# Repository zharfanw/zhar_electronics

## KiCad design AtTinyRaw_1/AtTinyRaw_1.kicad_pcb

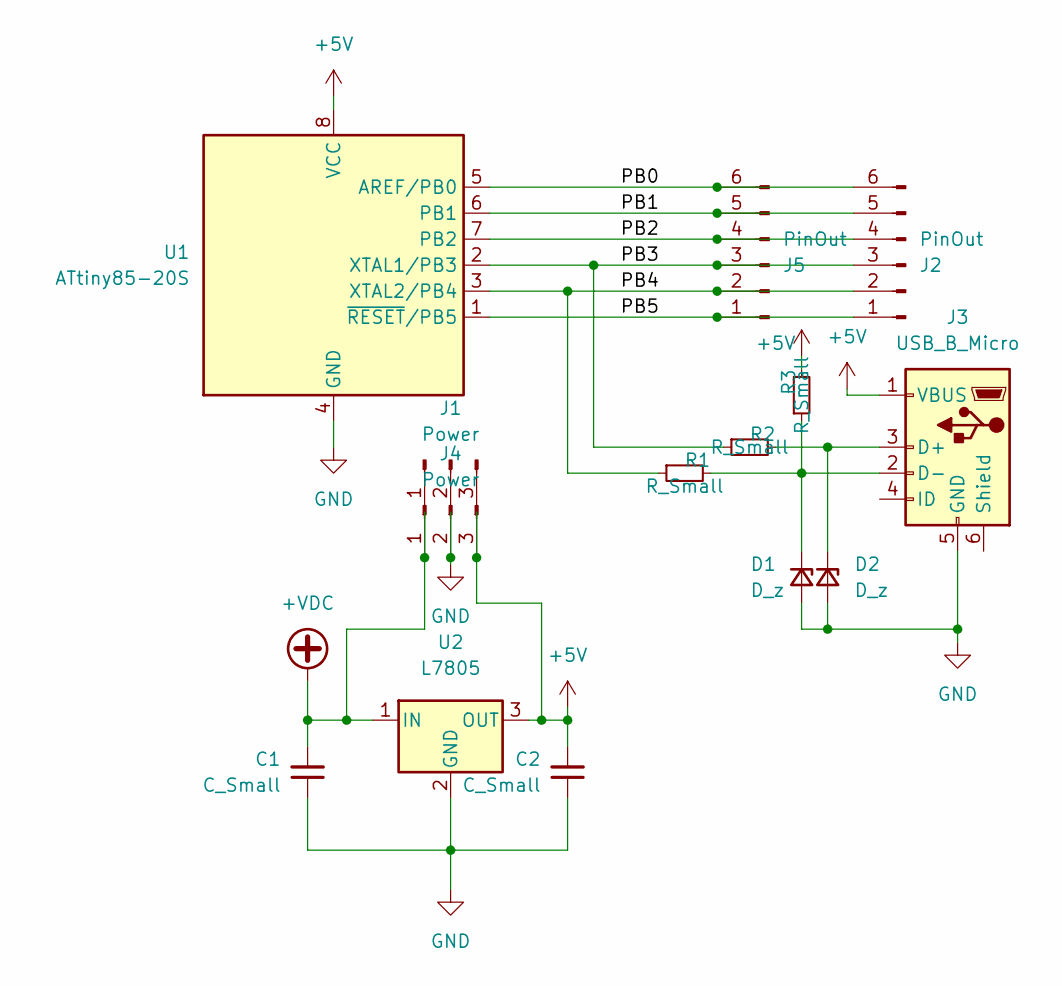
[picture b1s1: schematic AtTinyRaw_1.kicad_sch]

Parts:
C1, C2: C_Small; C_0805_2012Metric_Pad1.18x1.45mm_HandSolder
D1, D2: D_z; D_1206_3216Metric_Pad1.42x1.75mm_HandSolder
J1, J4: Power; PinSocket_1x03_P2.54mm_Vertical
J2, J5: PinOut; PinSocket_1x06_P2.54mm_Vertical
J3: USB_B_Micro; USB_Micro-AB_Molex_47590-0001
R1, R2, R3: R_Small; R_0805_2012Metric_Pad1.20x1.40mm_HandSolder
U1: ATtiny85-20S; SOIC-8W_5.3x5.3mm_P1.27mm
U2: L7805; TO-252-2

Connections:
+5V: C2.2, J1.3, J3.1 (VBUS), J4.3, R3.2, U1.8 (VCC), U2.3 (OUT)
+VDC: C1.2, J1.1, J4.1, U2.1 (IN)
/PB0: J2.6, J5.6, U1.5 (AREF/PB0)
/PB1: J2.5, J5.5, U1.6 (PB1)
/PB2: J2.4, J5.4, U1.7 (PB2)
/PB3: J2.3, J5.3, R2.1, U1.2 (XTAL1/PB3)
/PB4: J2.2, J5.2, R1.1, U1.3 (XTAL2/PB4)
/PB5: J2.1, J5.1, U1.1 (~RESET/PB5)
GND: C1.1, C2.1, D1.2 (A), D2.2 (A), J1.2, J3.5 (GND), J4.2, U1.4 (GND), U2.2 (GND)
unnamed: D1.1 (K), J3.2 (D-), R1.2, R3.1
unnamed: D2.1 (K), J3.3 (D+), R2.2

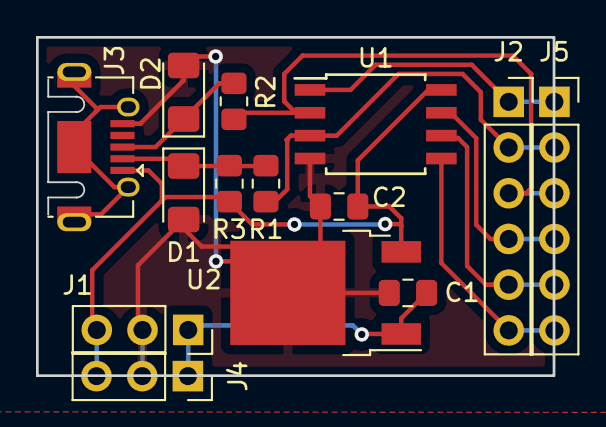
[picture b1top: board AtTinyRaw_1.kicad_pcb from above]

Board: 2 copper layers, 28.7 x 18.8 mm, 14 parts (0 on the bottom side), 11 nets.

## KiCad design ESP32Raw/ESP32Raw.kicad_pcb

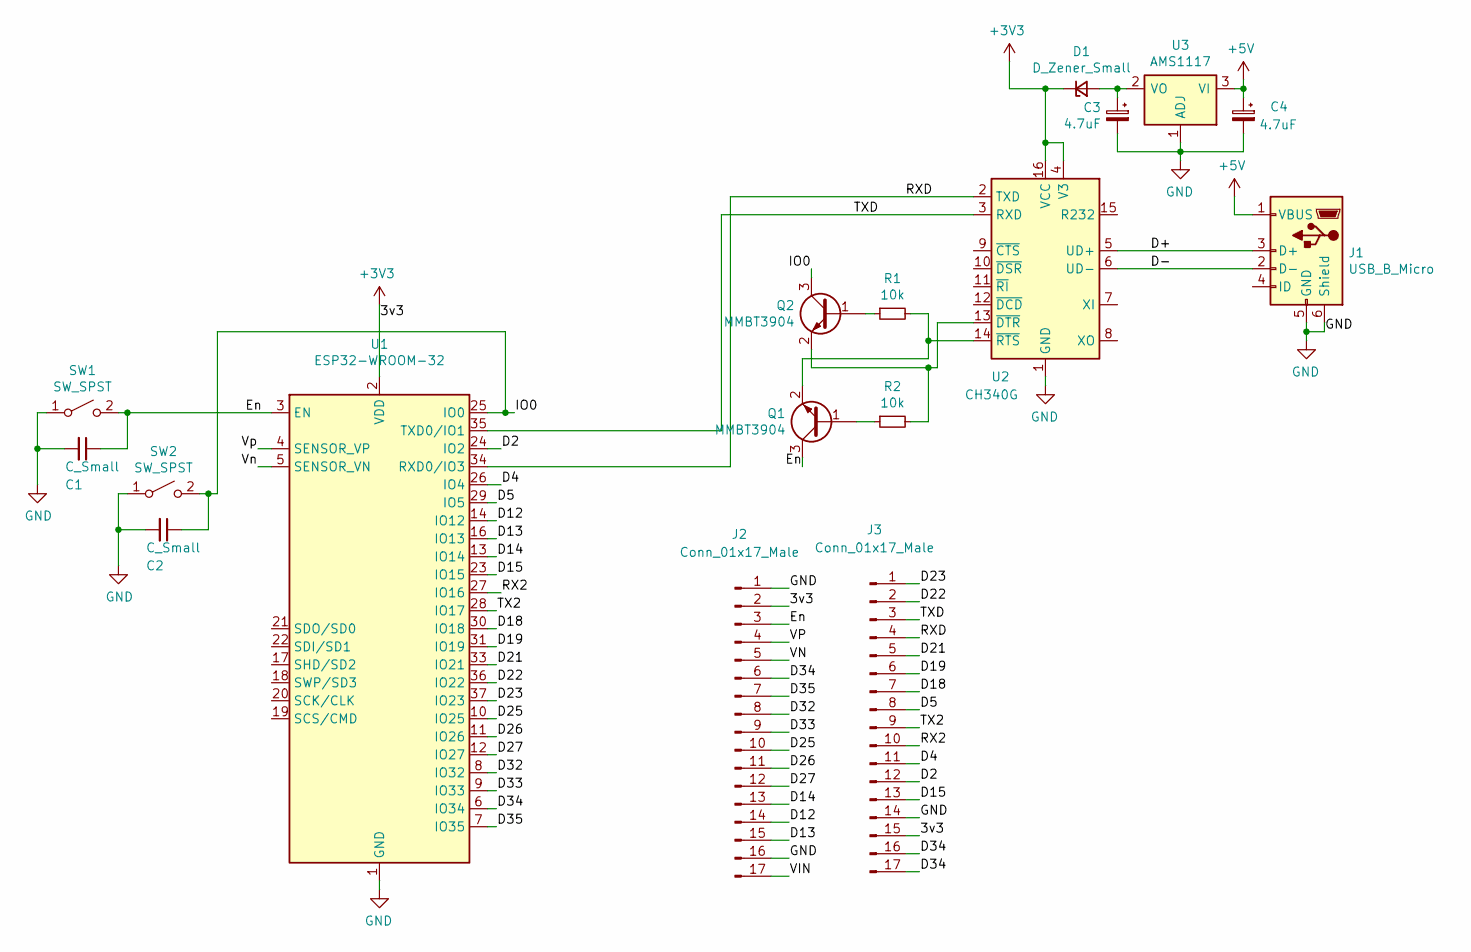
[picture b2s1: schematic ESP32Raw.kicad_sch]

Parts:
C1, C2: C_Small; C_0805_2012Metric_Pad1.18x1.45mm_HandSolder
C3, C4: 4.7uF; C_0805_2012Metric_Pad1.18x1.45mm_HandSolder
D1: D_Zener_Small; D_SOD-323
J1: USB_B_Micro; USB_Micro-B_Molex-105017-0001
J2, J3: Conn_01x17_Male; PinHeader_1x17_P2.54mm_Vertical
Q1, Q2: MMBT3904; SOT-23
R1, R2: 10k; R_0805_2012Metric_Pad1.20x1.40mm_HandSolder
SW1, SW2: SW_SPST; SW_SPST_EVQPE1
U1: ESP32-WROOM-32
U2: CH340G; SOIC-16_3.9x9.9mm_P1.27mm
U3: AMS1117; SOT-223-3_TabPin2

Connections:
+3V3: D1.1 (K), J2.2, J3.15, U1.2 (VDD), U2.4 (V3), U2.16 (VCC)
+5V: C4.1, J1.1 (VBUS), U3.3 (VI)
/D2: J3.12, U1.24 (IO2)
/D4: J3.11, U1.26 (IO4)
/D5: J3.8, U1.29 (IO5)
/D12: J2.14, U1.14 (IO12)
/D13: J2.15, U1.16 (IO13)
/D14: J2.13, U1.13 (IO14)
/D15: J3.13, U1.23 (IO15)
/D18: J3.7, U1.30 (IO18)
/D19: J3.6, U1.31 (IO19)
/D21: J3.5, U1.33 (IO21)
/D22: J3.2, U1.36 (IO22)
/D23: J3.1, U1.37 (IO23)
/D25: J2.10, U1.10 (IO25)
/D26: J2.11, U1.11 (IO26)
/D27: J2.12, U1.12 (IO27)
/D32: J2.8, U1.8 (IO32)
/D33: J2.9, U1.9 (IO33)
/D34: J2.6, J3.16, J3.17, U1.6 (IO34)
/D35: J2.7, U1.7 (IO35)
/D+: J1.3 (D+), U2.5 (UD+)
/D-: J1.2 (D-), U2.6 (UD-)
/En: C1.1, J2.3, Q1.3 (C), SW1.2 (B), U1.3 (EN)
/IO0: C2.1, Q2.3 (C), SW2.2 (B), U1.25 (IO0)
/RX2: J3.10, U1.27 (IO16)
/RXD: J3.4, U1.34 (RXD0/IO3), U2.2 (TXD)
/TX2: J3.9, U1.28 (IO17)
/TXD: J3.3, U1.35 (TXD0/IO1), U2.3 (RXD)
/VIN: J2.17
/VN: J2.5
/VP: J2.4
/Vn: U1.5 (SENSOR_VN)
/Vp: U1.4 (SENSOR_VP)
GND: C1.2, C2.2, C3.2, C4.2, J1.5 (GND), J1.6 (Shield), J2.1, J2.16, J3.14, SW1.1 (A), SW2.1 (A), U1.1 (GND), U1.15 (GND), U1.38 (GND), U1.39 (GND), U2.1 (GND), U3.1 (ADJ)
unnamed: C3.1, D1.2 (A), U3.2 (VO)
unnamed: Q1.1 (B), R2.1
unnamed: Q1.2 (E), R1.2, U2.14 (~RTS)
unnamed: Q2.1 (B), R1.1
unnamed: Q2.2 (E), R2.2, U2.13 (~DTR)

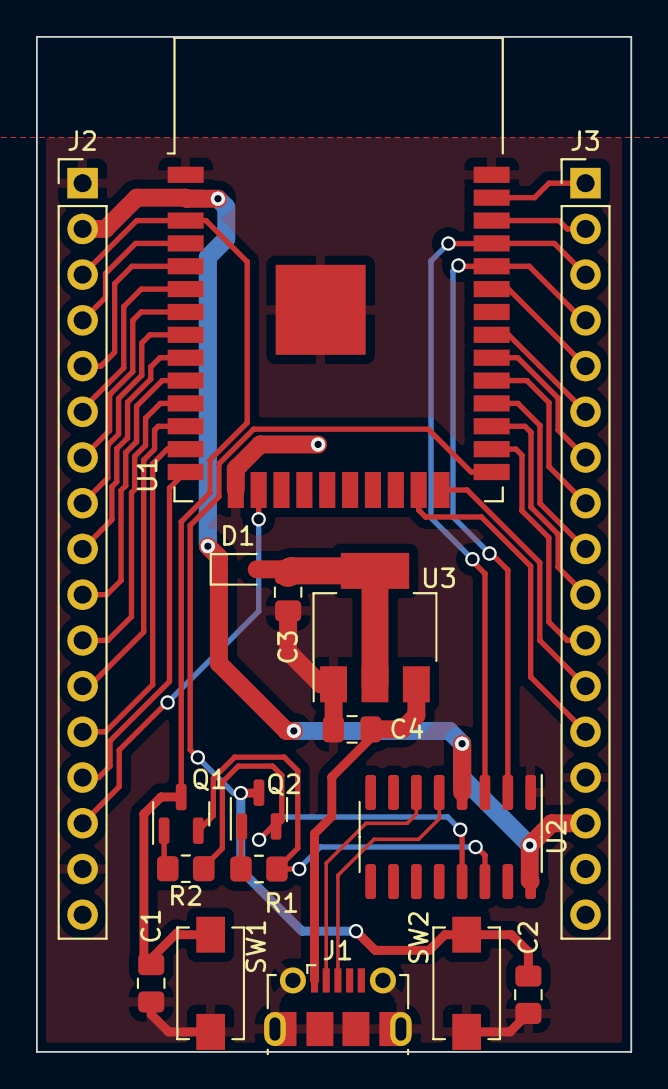
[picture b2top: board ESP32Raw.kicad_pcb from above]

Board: 2 copper layers, 33.0 x 56.4 mm, 17 parts (0 on the bottom side), 35 nets.

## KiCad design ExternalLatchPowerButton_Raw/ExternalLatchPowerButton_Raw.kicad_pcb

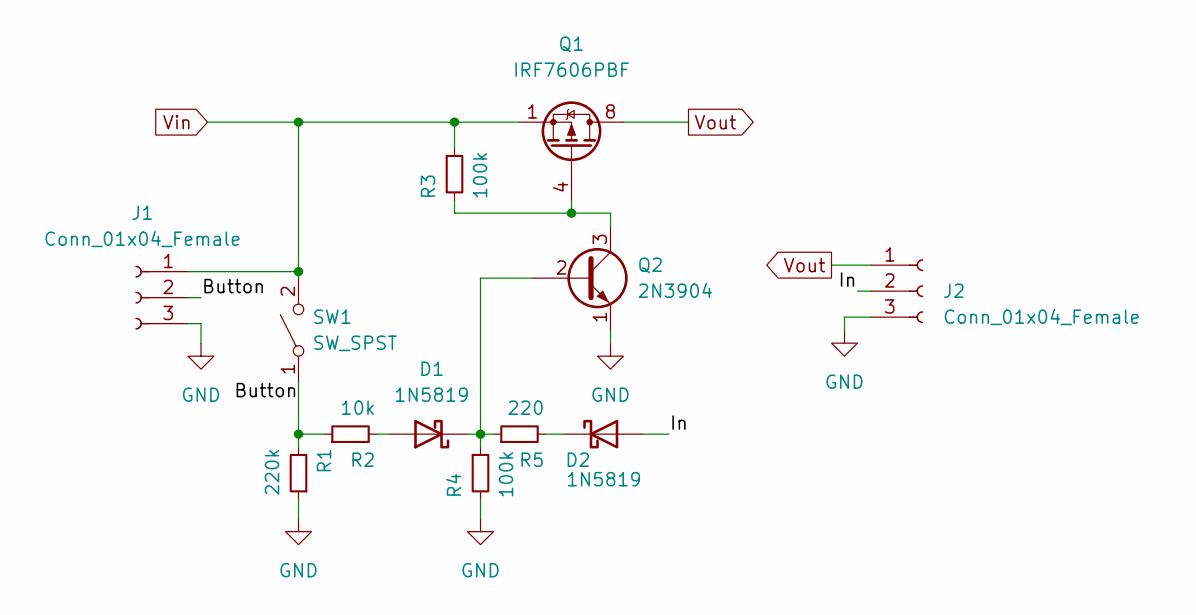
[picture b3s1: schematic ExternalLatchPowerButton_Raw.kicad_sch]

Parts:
D1, D2: 1N5819; D_SOD-123
J1, J2: Conn_01x04_Female; PinSocket_1x03_P2.54mm_Vertical
Q1: IRF7606PBF; MSOP-8_3x3mm_P0.65mm
Q2: 2N3904; SOT-23
R1: 220k; R_0805_2012Metric
R2: 10k; R_0805_2012Metric
R3, R4: 100k; R_0805_2012Metric
R5: 220; R_0805_2012Metric
SW1: SW_SPST; SW_SPST_SKQG_WithoutStem

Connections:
/Button: J1.2, R1.2, R2.1, SW1.1 (A)
/In: D2.2 (A), J2.2
GND: J1.3, J2.3, Q2.1 (E), R1.1, R4.2
unnamed: D1.1 (K), Q2.2 (B), R4.1, R5.1
unnamed: D1.2 (A), R2.2
unnamed: D2.1 (K), R5.2
unnamed: Q1.4 (G), Q2.3 (C), R3.2
Vin: J1.1, Q1.1 (S), Q1.2 (S), Q1.3 (S), R3.1, SW1.2 (B)
Vout: J2.1, Q1.5 (D), Q1.6 (D), Q1.7 (D), Q1.8 (D)

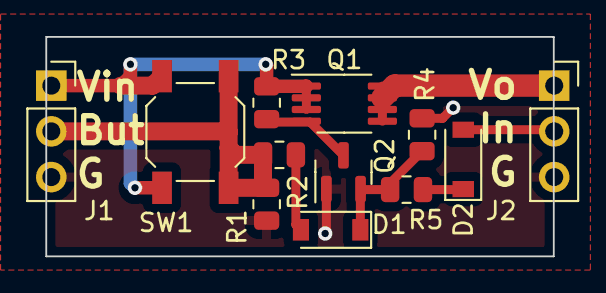
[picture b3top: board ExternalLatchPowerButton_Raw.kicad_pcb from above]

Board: 2 copper layers, 28.2 x 12.2 mm, 12 parts (0 on the bottom side), 9 nets.

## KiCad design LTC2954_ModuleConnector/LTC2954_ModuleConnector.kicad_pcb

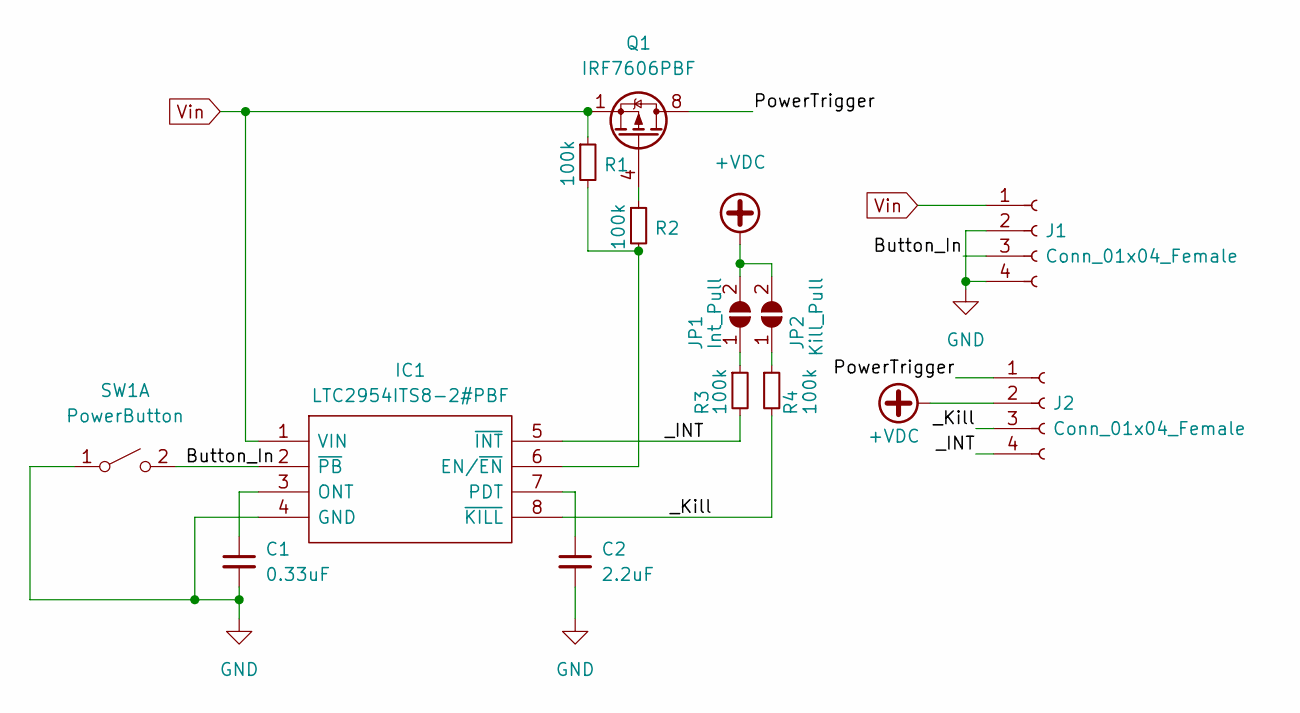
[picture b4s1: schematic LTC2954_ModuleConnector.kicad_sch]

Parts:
C1: 0.33uF; C_0805_2012Metric
C2: 2.2uF; C_0805_2012Metric
IC1: LTC2954ITS8-2#PBF; SOT65P280X100-8N; Manufacturer_Part_Number LTC2954ITS8-2#PBF; Mouser Part Number 584-LTC2954ITS8-2PBF
J1, J2: Conn_01x04_Female; PinSocket_1x04_P2.54mm_Vertical
JP1: Int_Pull; SolderJumper-2_P1.3mm_Open_TrianglePad1.0x1.5mm
JP2: Kill_Pull; SolderJumper-2_P1.3mm_Open_TrianglePad1.0x1.5mm
Q1: IRF7606PBF; MSOP-8_3x3mm_P0.65mm
R1, R2, R3, R4: 100k; R_0805_2012Metric
SW1: PowerButton; SW_Push_1P1T_NO_CK_KMR2

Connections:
+VDC: J2.2, JP1.2 (B), JP2.2 (B)
/Button_In: IC1.2 (~PB), J1.3, SW1.2 (B)
/PowerTrigger: J2.1, Q1.5 (D), Q1.6 (D), Q1.7 (D), Q1.8 (D)
/_INT: IC1.5 (~INT), J2.4, R3.2
/_Kill: IC1.8 (~KILL), J2.3, R4.2
GND: C1.2, C2.2, IC1.4 (GND), J1.2, J1.4, SW1.1 (A)
unnamed: C1.1, IC1.3 (ONT)
unnamed: C2.1, IC1.7 (PDT)
unnamed: IC1.6 (EN/~EN), R1.2, R2.2
unnamed: JP1.1 (A), R3.1
unnamed: JP2.1 (A), R4.1
unnamed: Q1.4 (G), R2.1
Vin: IC1.1 (VIN), J1.1, Q1.1 (S), Q1.2 (S), Q1.3 (S), R1.1

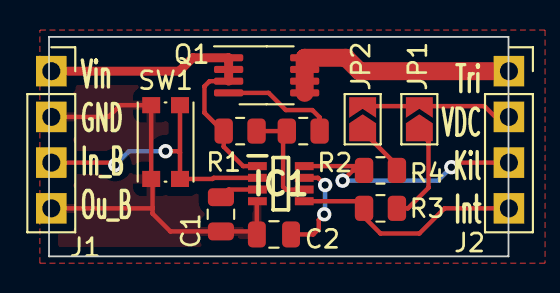
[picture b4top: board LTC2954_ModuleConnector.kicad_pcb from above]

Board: 2 copper layers, 25.5 x 12.2 mm, 13 parts (0 on the bottom side), 13 nets.

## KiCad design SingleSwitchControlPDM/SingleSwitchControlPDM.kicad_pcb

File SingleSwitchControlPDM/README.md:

# Single Switch Control PDM
Rangkaian Elektronik untuk mengontrol Arus listrik 
## Biaya

## Simulation

##

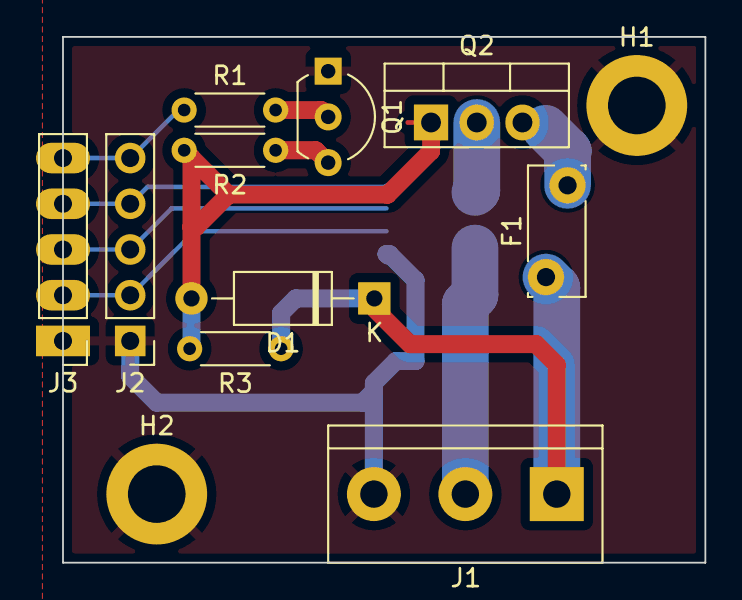
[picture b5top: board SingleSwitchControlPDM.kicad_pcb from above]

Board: 2 copper layers, 35.7 x 29.2 mm, 13 parts (1 on the bottom side), 12 nets.

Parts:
D1: D_Small; D_A-405_P10.16mm_Horizontal
F1: Fuse; Fuse_Bourns_MF-RG300
H1, H2: MountingHole_Pad; MountingHole_3.2mm_M3_DIN965_Pad
J1: Screw_Terminal_01x02; TerminalBlock_bornier-3_P5.08mm
J2, J3: Conn_01x05_Male; PinHeader_1x05_P2.54mm_Vertical
Q1: 2N2219; TO-92L_Inline_Wide
Q2: IRF9540N; TO-220-3_Vertical
R1, R2, R3: R_Small; R_Axial_DIN0204_L3.6mm_D1.6mm_P5.08mm_Horizontal
U1: ACS712xLCTR-30A; SOIC-8_3.9x4.9mm_P1.27mm

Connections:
+5V: J2.4, J3.4, U1.8 (VCC)
+VDC: D1.1 (K), F1.1, J1.1, R3.1
/2_30Amp: Q2.2 (D), U1.1 (IP+), U1.2 (IP+)
/3_30Amp: J1.2, U1.3 (IP-), U1.4 (IP-)
/30Amp: F1.2, Q2.3 (S)
/Filter: J2.2, J3.2, U1.6 (FILTER)
/Input: J2.5, J3.5, R1.1
/Vout: J2.3, J3.3, U1.7 (VIOUT)
GND: H1.1, H2.1, J1.3, J2.1, J3.1, Q1.1 (E), U1.5 (GND)
unnamed: D1.2 (A), Q2.1 (G), R2.2, R3.2
unnamed: Q1.2 (B), R1.2
unnamed: Q1.3 (C), R2.1

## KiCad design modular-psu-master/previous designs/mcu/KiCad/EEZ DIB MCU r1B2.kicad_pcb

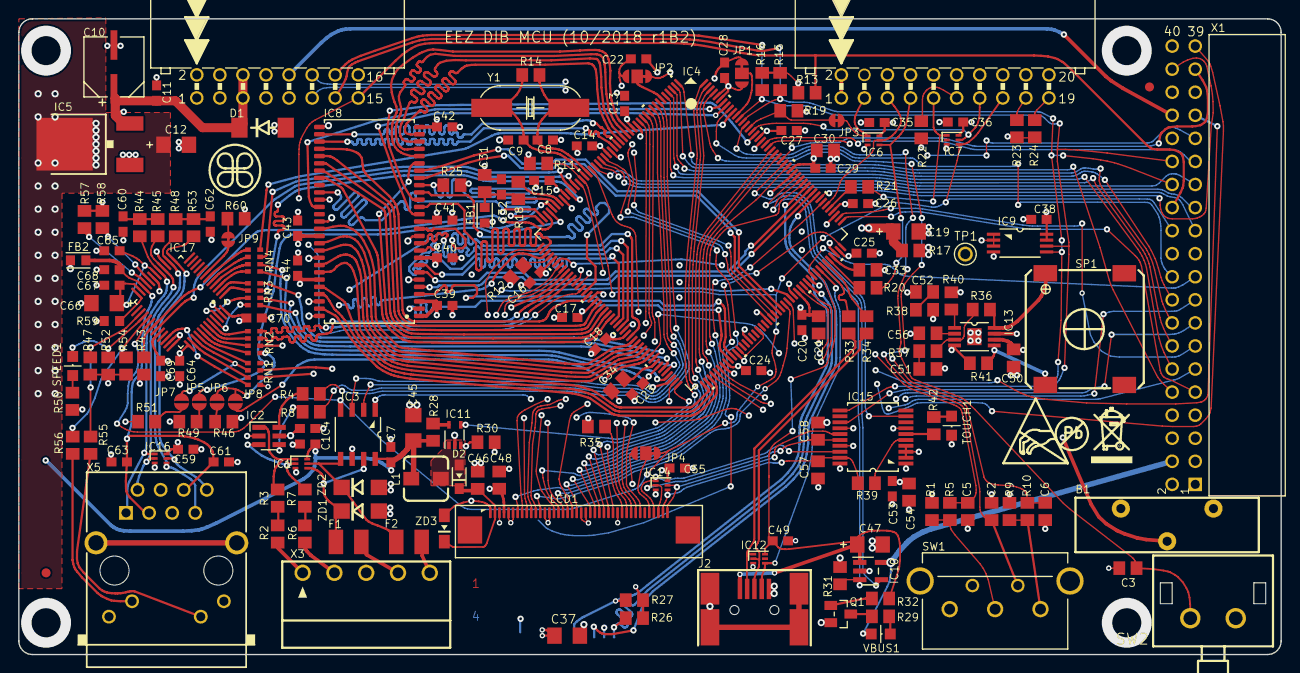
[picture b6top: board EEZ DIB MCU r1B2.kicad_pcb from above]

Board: 4 copper layers, 139.0 x 70.0 mm, 194 parts (0 on the bottom side), 233 nets.

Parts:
B1: DS1092-16-B6P
C1, C4, C7, C11, C13, C14, C15, C16, C17, C18, C20, C23, C24, C25, C26, C27, C28, C29, C32, C35, C36, C38, C39, C40, C41, C42, C43, C44, C49, C53, C55, C59, C60, C61, C62, C63, C64, C65, C67, C68, C69, C70: 100n; C0603
C2, C3, C5, C6, C57, C58: 10n; C0805
C8, C9: 18p; C0603
C10: EEEFK1V470P; CAPAE660X610N
C12, C19, C47: 4u7; EC1206
C21, C30, C31, C46, C50, C54: 1u; C0805
C22: N.C.; C0603
C33, C34, C48: 2u2; C0805
C37, C45: 4u7; C1206
C51, C52, C56: 470n; C0805
C66: 10u; EC1206
D1: SMBJ5.0A-TR; DO214AA
D2: RB751V40T1G or NSR0240; SOD323-R
EEZ_SIGNATURE: SIGNATURESMALL; SIGNATURE_5MM
F1, F2: 50mA; F1210
FB1, FB2: LCBA-600; BEAD0603
FM1, FM2: FIDUCIAL
IC1, IC6, IC7, IC12, IC14, IC16: TPD4E001DRLR; DRL6
IC2: SN74LVC2G34DBVR; DBV6
IC3: BTS3408G; SOIC127P600X173-8N
IC4: STM32F769IGT6; LQFP-176_24X24MM
IC5: LD1117ADT33TR; DPACK
IC8: IS42S16400J; TSOPII-54
IC9: BR24G64FVT-3AGE2; PW8_TSSOP8
IC10: TPS2051BDBVR; DBV5
IC11: TPS61169DCKR; DCK5
IC13: TPA6205A1DGN; SOP65P490X110-9N
IC15: AR1021-I/SS; SOP65P780X200-20N
IC17: DP83848CVV_NOPB; PT48
J1: 503398-1892; 5033981892
J2: 67803-8020; 678038020
JP1, JP2, JP4: JP3-CUT
JP3, JP9: JP2-NOCUT
JP5, JP6, JP7, JP8: JP2-CUT
L1: DLG-0403-4R7; DE0403
LCD1: PCA-6-LA-40-HL-3; FPC_40
Q1: MMBT5551; SOT23-BEC
R1, R2, R3, R6, R7, R9, R13, R15, R16, R42: 4K7; R0805
R4, R8: 1K; R0805
R5, R10, R11, R12, R22, R23, R24, R25, R35, R37, R38: 10K; R0805
R14: 1M; R0805
R17: 0R; R0805
R18: 47R; R0805
R19, R26, R27, R29, R31, R32, R40: 47K; R0805
R20, R21, R33, R34: 22R; R0805
R28, R30: 10R; R0805
R36, R39, R41: 20K; R0805
R43: 1K5; R0805
R44, R45, R48, R53: 49R9; R0805
R46, R47, R49, R51, R52, R54, R57, R58, R60: 2K2; R0805
R50, R55, R56: 220R; R0805
R59: 4K87; R0603
RN1, RN2, RN3, RN4: DR1206-33R-4/8; CAY16
SP1: LD-BZEL-M1313
SPEED1: LTST-C170YKT; LED_0805
SW1: PEC16-2215F-S0024; PEC16-2215F
SW2: TL1100CF160Q; TL1100C
TOUCH1: HSMY-C170; LED_0805
TP1: PCB_TEST_TABSHIELD; PCB_SHIELD_TAB
U$1: RECYCLE_BIN1_8
U$5: PB_SMALL
U$6: ESD_SYMBOL
VBUS1: HSMG-C170; LED_0805
X1: ZL263-40DG
X2: ZL231-16KG; ML16L
X3: 1844249; MC1,5_5-G-3,5
X4: ZL231-20KG; ML20L
X5: LMJTAB881243M-L; RJ45-TRAFO-LED
Y1: 10MHz; HC-49_4H
ZD1, ZD2: SMAJ18A; DO214AC
ZD3: BZX384-B30.115; SOD323-W

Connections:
+3V3: C4.1, C12.+, C35.1, C36.1, C37.1, C38.2, C39.1, C40.1, C41.1, C42.1, C43.1, C44.1, C48.1, C50.2, C53.2, C54.2, C55.2, C59.1, C69.1, C70.1, FB2.P$1, IC2.5, IC5.4, IC6.6, IC7.6, IC8.1, IC8.3, IC8.9, IC8.14, IC8.27, IC8.43, IC8.49, IC9.1, IC9.2, IC9.3, IC9.7, IC9.8, IC13.6, IC14.6, IC15.1, IC16.6, IC17.32, IC17.48, J1.4, LCD1.4, R1.1, R9.1, R13.1, R15.1, R16.1, R17.1, R19.1, R25.1, R26.1, R27.1, R31.2, R35.2, R40.2, R43.2, R47.1, R50.1, R51.1, R52.1, R54.1, R57.1, R58.1, R60.1, X1.32, X2.16, X4.1, X4.2, X5.9, X5.12
+3V3(A): C61.2, C63.2, C68.1, FB2.P$2, IC17.22, X5.3, X5.6
+5V: C1.1, C7.2, C10.1, C11.1, C45.1, D1.C, IC1.6, IC3.8, IC5.3, IC10.5, L1.1, R28.1, VBUS1.A, X1.3, X1.4, X2.5, X2.6
+12V: X1.5, X1.6, X2.3, X2.4
/Ethernet PHY/ETH_COL: IC4.47, RN2.2
/Ethernet PHY/ETH_CRS: IC4.40, JP5.1, RN1.4
/Ethernet PHY/ETH_MDC: IC4.33, IC17.31
/Ethernet PHY/ETH_MDIO: IC4.42, IC17.30, R43.1
/Ethernet PHY/ETH_RX+: IC16.4, IC17.14, R48.2, X5.7
/Ethernet PHY/ETH_RX-: IC16.5, IC17.13, R53.1, X5.8
/Ethernet PHY/ETH_RXD0: IC4.54, RN2.3
/Ethernet PHY/ETH_RXD1: IC4.55, RN2.4
/Ethernet PHY/ETH_RXD2: IC4.83, RN3.1
/Ethernet PHY/ETH_RXD3: IC4.84, RN3.2
/Ethernet PHY/ETH_RX_CLK: IC4.41, RN1.2
/Ethernet PHY/ETH_RX_DV: IC4.53, RN1.3
/Ethernet PHY/ETH_TX+: IC16.1, IC17.17, R44.2, X5.1
/Ethernet PHY/ETH_TX-: IC16.2, IC17.16, R45.1, X5.2
/Ethernet PHY/ETH_TXD0: IC4.85, RN4.1
/Ethernet PHY/ETH_TXD1: IC4.86, RN4.2
/Ethernet PHY/ETH_TXD2: IC4.34, RN4.3
/Ethernet PHY/ETH_TXD3: IC4.167, RN4.4
/Ethernet PHY/ETH_TX_CLK: IC4.35, RN3.3
/Ethernet PHY/ETH_TX_EN: IC4.80, RN3.4
/Ethernet PHY/LED_ACT: IC17.26, R47.2, R55.2
/Ethernet PHY/LED_LINK: IC17.28, R54.2, R56.2
/Ethernet PHY/LED_SPEED: IC17.27, R52.2, SPEED1.C
/Ethernet PHY/MCLK_25: IC4.122, RN1.1
/I/O connectors, encoders, user SW/+VAUX: X1.34, X2.10
/I/O connectors, encoders, user SW/ENC_A: C5.2, IC4.119, R5.1
/I/O connectors, encoders, user SW/ENC_B: C6.1, IC4.120, R10.1
/I/O connectors, encoders, user SW/ENC_SW: C2.2, IC4.173, SW1.E
/I/O connectors, encoders, user SW/USER_SW: C3.2, IC4.163, SW2.1
/SDRAM, JTAG, SD card, EEPROM/DBGACK: R24.1, X4.19
/SDRAM, JTAG, SD card, EEPROM/DBGRQ: R23.1, X4.17
/SDRAM, JTAG, SD card, EEPROM/FMC_A0: IC4.16, IC8.23
/SDRAM, JTAG, SD card, EEPROM/FMC_A1: IC4.17, IC8.24
/SDRAM, JTAG, SD card, EEPROM/FMC_A2: IC4.18, IC8.25
/SDRAM, JTAG, SD card, EEPROM/FMC_A3: IC4.19, IC8.26
/SDRAM, JTAG, SD card, EEPROM/FMC_A4: IC4.20, IC8.29
/SDRAM, JTAG, SD card, EEPROM/FMC_A5: IC4.21, IC8.30
/SDRAM, JTAG, SD card, EEPROM/FMC_A6: IC4.60, IC8.31
/SDRAM, JTAG, SD card, EEPROM/FMC_A7: IC4.63, IC8.32
/SDRAM, JTAG, SD card, EEPROM/FMC_A8: IC4.64, IC8.33
/SDRAM, JTAG, SD card, EEPROM/FMC_A9: IC4.65, IC8.34
/SDRAM, JTAG, SD card, EEPROM/FMC_A10: IC4.66, IC8.22
/SDRAM, JTAG, SD card, EEPROM/FMC_A11: IC4.67, IC8.35
/SDRAM, JTAG, SD card, EEPROM/FMC_BA0: IC4.112, IC8.20
/SDRAM, JTAG, SD card, EEPROM/FMC_BA1: IC4.113, IC8.21
/SDRAM, JTAG, SD card, EEPROM/FMC_D0: IC4.97, IC8.2
/SDRAM, JTAG, SD card, EEPROM/FMC_D1: IC4.98, IC8.4
/SDRAM, JTAG, SD card, EEPROM/FMC_D2: IC4.142, IC8.5
/SDRAM, JTAG, SD card, EEPROM/FMC_D3: IC4.143, IC8.7
/SDRAM, JTAG, SD card, EEPROM/FMC_D4: IC4.68, IC8.8
/SDRAM, JTAG, SD card, EEPROM/FMC_D5: IC4.69, IC8.10
/SDRAM, JTAG, SD card, EEPROM/FMC_D6: IC4.70, IC8.11
/SDRAM, JTAG, SD card, EEPROM/FMC_D7: IC4.73, IC8.13
/SDRAM, JTAG, SD card, EEPROM/FMC_D8: IC4.74, IC8.42
/SDRAM, JTAG, SD card, EEPROM/FMC_D9: IC4.75, IC8.44
/SDRAM, JTAG, SD card, EEPROM/FMC_D10: IC4.76, IC8.45
/SDRAM, JTAG, SD card, EEPROM/FMC_D11: IC4.77, IC8.47
/SDRAM, JTAG, SD card, EEPROM/FMC_D12: IC4.78, IC8.48
/SDRAM, JTAG, SD card, EEPROM/FMC_D13: IC4.89, IC8.50
/SDRAM, JTAG, SD card, EEPROM/FMC_D14: IC4.90, IC8.51
/SDRAM, JTAG, SD card, EEPROM/FMC_D15: IC4.91, IC8.53
/SDRAM, JTAG, SD card, EEPROM/FMC_NBL0: IC4.169, IC8.15
/SDRAM, JTAG, SD card, EEPROM/FMC_NBL1: IC4.170, IC8.39
/SDRAM, JTAG, SD card, EEPROM/FMC_SDCKE0: IC4.43, IC8.37
/SDRAM, JTAG, SD card, EEPROM/FMC_SDCLK: IC4.116, IC8.38
/SDRAM, JTAG, SD card, EEPROM/FMC_SDNCAS: IC4.160, IC8.17
/SDRAM, JTAG, SD card, EEPROM/FMC_SDNE0: IC4.44, IC8.19, R25.2
/SDRAM, JTAG, SD card, EEPROM/FMC_SDNRAS: IC4.59, IC8.18
/SDRAM, JTAG, SD card, EEPROM/FMC_SDNWE: IC4.46, IC8.16
/SDRAM, JTAG, SD card, EEPROM/RTCK: R22.1, X4.11
/SDRAM, JTAG, SD card, EEPROM/SDMMC1_CK: IC4.141, J1.5
/SDRAM, JTAG, SD card, EEPROM/SDMMC1_CMD: IC4.144, J1.3, R27.2
/SDRAM, JTAG, SD card, EEPROM/SDMMC1_D0: IC4.121, J1.7, R26.2
/SDRAM, JTAG, SD card, EEPROM/SD_DETECT: IC4.24, J1.SW1
/SDRAM, JTAG, SD card, EEPROM/SYS_JTCK-SWCLK: IC4.137, R21.1
/SDRAM, JTAG, SD card, EEPROM/SYS_JTDI: IC4.138, IC6.5, X4.5
/SDRAM, JTAG, SD card, EEPROM/SYS_JTDO-SWO: IC4.161, IC7.5, X4.13
/SDRAM, JTAG, SD card, EEPROM/SYS_JTMS-SWDIO: IC4.128, R20.1
/SDRAM, JTAG, SD card, EEPROM/SYS_JTRST: IC4.162, JP3.1, R19.2
/SDRAM, JTAG, SD card, EEPROM/TCK: IC7.1, R21.2, X4.9
/SDRAM, JTAG, SD card, EEPROM/TMS: IC6.4, R20.2, X4.7
/STM32F7 MCU/BOOT0: IC4.166, JP1.COM
/STM32F7 MCU/BYPASS_REG: IC4.48, R12.2
/STM32F7 MCU/DAC_OUT1: C52.2, IC4.50
/STM32F7 MCU/IRQ_TOUCH: IC4.151, IC15.9
/STM32F7 MCU/LTDC_B2: IC4.150, LCD1.23
/STM32F7 MCU/LTDC_B3: IC4.154, LCD1.24
/STM32F7 MCU/LTDC_B4: IC4.155, LCD1.25
/STM32F7 MCU/LTDC_B5: IC4.174, LCD1.26
/STM32F7 MCU/LTDC_B6: IC4.175, LCD1.27
/STM32F7 MCU/LTDC_B7: IC4.176, LCD1.28
/STM32F7 MCU/LTDC_CLK: IC4.115, LCD1.30
/STM32F7 MCU/LTDC_DE: IC4.28, LCD1.34
/STM32F7 MCU/LTDC_G2: IC4.52, LCD1.15
/STM32F7 MCU/LTDC_G3: IC4.153, LCD1.16
/STM32F7 MCU/LTDC_G4: IC4.45, LCD1.17
/STM32F7 MCU/LTDC_G5: IC4.132, LCD1.18
/STM32F7 MCU/LTDC_G6: IC4.13, LCD1.19
/STM32F7 MCU/LTDC_G7: IC4.145, LCD1.20
/STM32F7 MCU/LTDC_HSYNC: IC4.12, LCD1.32
/STM32F7 MCU/LTDC_R2: IC4.139, LCD1.7
/STM32F7 MCU/LTDC_R3: IC4.56, LCD1.8
/STM32F7 MCU/LTDC_R4: IC4.51, LCD1.9
/STM32F7 MCU/LTDC_R5: IC4.32, LCD1.10
/STM32F7 MCU/LTDC_R6: IC4.57, LCD1.11
/STM32F7 MCU/LTDC_R7: IC4.114, LCD1.12
/STM32F7 MCU/LTDC_VSYNC: IC4.11, LCD1.33
/STM32F7 MCU/RCC_OSC_IN: C8.2, IC4.29, R14.2, Y1.2
/STM32F7 MCU/RCC_OSC_OUT: C9.2, IC4.30, R14.1, Y1.1
/STM32F7 MCU/TFT_BRIGHTNESS: IC4.88, IC11.4
/STM32F7 MCU/USB_OTG_FS_D_N: IC4.126, R33.2
/STM32F7 MCU/USB_OTG_FS_D_P: IC4.127, R34.2
/STM32F7 MCU/USB_OTG_FS_ID: IC4.125, IC12.4, J2.4
/STM32F7 MCU/USB_OTG_FS_PSO: IC4.147, IC10.4
/STM32F7 MCU/USB_OTG_FS_VBUS: C47.+, C49.2, IC4.124, IC10.1, IC12.6, J2.1, R32.1
/STM32F7 MCU/VBAT: IC4.6, JP2.COM
/STM32F7 MCU/VCAP1: C34.1, IC4.81
/STM32F7 MCU/VCAP2: C33.1, IC4.129
/STM32F7 MCU/VDDA: C31.1, C32.1, FB1.P$2, IC4.39, R18.2
/STM32F7 MCU/VREF+: IC4.38, R18.1
/STM32F7 MCU/~USB_OTG_FS_OC: IC4.146, IC10.3, R31.1
/TFT, Audio, USB/LCD_DISP: LCD1.31, R35.1
/TFT, Audio, USB/LTDC_RESET: JP4.COM, LCD1.36
/TFT, Audio, USB/SPKR+: IC13.5, R41.1, SP1.-
/TFT, Audio, USB/SPKR-: IC13.8, R36.1, SP1.+
/TFT, Audio, USB/Touch_XL: C57.1, IC14.4, IC15.19, LCD1.39, R39.2
/TFT, Audio, USB/Touch_XR: IC14.1, IC15.18, LCD1.37
/TFT, Audio, USB/Touch_YD: C58.1, IC14.2, IC15.16, LCD1.38
/TFT, Audio, USB/Touch_YU: IC14.5, IC15.15, LCD1.40
/TFT, Audio, USB/USB_D_N: IC12.1, J2.2, R33.1
/TFT, Audio, USB/USB_D_P: IC12.2, J2.3, R34.1
/TFT, Audio, USB/VLED+: C46.1, D2.C, LCD1.2, ZD3.C
/TFT, Audio, USB/VLED-: IC11.3, LCD1.1, R30.1, ZD3.A
/TFT, Audio, USB/VLED_SW: D2.A, IC11.1, L1.2
/TFT, Audio, USB/~AUDIO_SHDN: IC13.1, R40.1
DIN1: IC4.7, R4.2
DIN2: IC4.8, R8.2
DOUT1: IC3.2, IC4.9
DOUT2: IC3.3, IC4.10
GND: B1.1, B1.3, C1.2, C2.1, C3.1, C4.2, C5.1, C6.2, C7.1, C8.1, C9.1, C10.2, C11.2, C12.-, C13.2, C14.2, C15.2, C16.2, C17.2, C18.2, C19.-, C20.2, C21.2, C22.2, C23.2, C24.2, C25.2, C26.2, C27.2, C28.2, C29.2, C30.2, C31.2, C32.2, C33.2, C34.2, C35.2, C36.2, C37.2, C38.1, C39.2, C40.2, C41.2, C42.2, C43.2, C44.2, C45.2, C46.2, C47.-, C48.2, C49.1, C50.1, C51.2, C53.1, C54.1, C55.1, C56.1, C57.2, C58.2, C59.2, C60.2, C61.1, C62.2, C63.1, C64.2, C65.2, C66.-, C67.2, C68.2, C69.2, C70.2, D1.A, IC1.3, IC2.2, IC3.6, IC4.14, IC4.22, IC4.37, IC4.61, IC4.71, IC4.95, IC4.103, IC4.109, IC4.117, IC4.130, IC4.135, IC4.148, IC4.158, IC5.1, IC6.3, IC7.3, IC8.6, IC8.12, IC8.28, IC8.41, IC8.46, IC8.52, IC8.54, IC9.4, IC10.2, IC11.2, IC12.3, IC13.7, IC13.TP, IC14.3, IC15.2, IC15.3, IC15.4, IC15.7, IC15.14, IC15.17, IC15.20, IC16.3, IC17.15, IC17.19, IC17.35, IC17.36, IC17.47, J1.6, J1.S, J1.SW2, J2.5, JP1.NC, JP4.NO, LCD1.3, LCD1.5, LCD1.6, LCD1.13, LCD1.14, LCD1.21, LCD1.22, LCD1.29, Q1.E, R12.1, R22.2, R23.2, R24.2, R30.2, R46.1, R49.1, R59.1, SW1.C, SW1.D, SW1.GND1, SW1.GND2, SW2.2, TOUCH1.C, TP1.1, X1.1, X1.2, X1.7, X1.8, X1.21, X1.22, X1.35, X1.36, X1.40, X2.7, X2.8, X2.9, X3.3, X4.4, X4.6, X4.8, X4.10, X4.12, X4.14, X4.16, X4.18, X4.20, X5.4, X5.5, ZD1.A, ZD2.A
I2C1_SCL: IC4.164, IC9.5, IC15.11, R15.2, X1.28, X2.13
I2C1_SDA: IC4.165, IC9.6, IC15.13, R16.2, X1.30, X2.14
unnamed: B1.2, JP2.NC
unnamed: C51.1, R37.2
unnamed: C52.1, R38.2
unnamed: C56.2, IC13.2
unnamed: C60.1, R44.1, R45.2
unnamed: C62.1, R48.1, R53.2
unnamed: C64.1, C65.1, C66.+, C67.1, IC17.18, IC17.23, IC17.37
unnamed: F1.1, X3.4
unnamed: F1.2, IC1.4, IC3.7, ZD1.C
unnamed: F2.1, X3.5
unnamed: F2.2, IC1.5, IC3.5, ZD2.C
unnamed: IC1.1, IC2.1, R3.2
unnamed: IC1.2, IC2.3, R7.2
unnamed: IC2.4, R8.1
unnamed: IC2.6, R4.1
unnamed: IC4.100, IC4.106
unnamed: IC6.1, JP3.2, X4.3
unnamed: IC11.5, R28.2
unnamed: IC13.3, R36.2, R37.1
unnamed: IC13.4, R38.1, R41.2
unnamed: IC15.5, R39.1
unnamed: IC15.6, R42.2
unnamed: IC17.1, RN3.6
unnamed: IC17.2, RN3.5
unnamed: IC17.3, RN4.8
unnamed: IC17.4, RN4.7
unnamed: IC17.5, RN4.6
unnamed: IC17.6, RN4.5
unnamed: IC17.7, JP9.2
unnamed: IC17.20, R58.2
unnamed: IC17.21, R57.2
unnamed: IC17.24, R59.2
unnamed: IC17.34, RN1.8
unnamed: IC17.38, RN1.7
unnamed: IC17.39, JP7.2, RN1.6
unnamed: IC17.40, RN1.5
unnamed: IC17.41, RN2.8
unnamed: IC17.42, RN2.7
unnamed: IC17.43, RN2.6
unnamed: IC17.44, RN2.5
unnamed: IC17.45, RN3.8
unnamed: IC17.46, RN3.7
unnamed: JP5.2, R49.2
unnamed: JP6.1, JP8.1, RN2.1
unnamed: JP6.2, R46.2
unnamed: JP7.1, R51.2
unnamed: JP9.1, R60.2
unnamed: Q1.B, R32.2
unnamed: Q1.C, R29.1
unnamed: R1.2, R5.2, SW1.B
unnamed: R2.1, X3.1
unnamed: R2.2, R3.1
unnamed: R6.1, X3.2
unnamed: R6.2, R7.1
unnamed: R9.2, R10.2, SW1.A
unnamed: R29.2, VBUS1.C
unnamed: R42.1, TOUCH1.A
unnamed: R50.2, SPEED1.A
unnamed: R55.1, X5.11
unnamed: R56.1, X5.10
OE_SYNC: IC4.94, X1.39
OUT_PAR: IC4.140, X1.38
OUT_SER: IC4.152, X1.37
PE: J2.SH1, J2.SH1.1, J2.SH2, J2.SH2.2, X2.1, X2.2, X5.SH, X5.SH2
PWR_DIRECT: IC4.110, X2.12
PWR_SSTART: IC4.111, X2.11
SPI2_CLK: IC4.133, X1.9
SPI2_CSA: IC4.93, X1.15
SPI2_CSB: IC4.92, X1.17
SPI2_IRQ: IC4.123, X1.19
SPI2_MISO: IC4.87, X1.11
SPI2_MOSI: IC4.134, X1.13
SPI4_CLK: IC4.1, X1.10
SPI4_CSA: IC4.2, X1.16
SPI4_CSB: IC4.3, X1.18
SPI4_IRQ: IC4.168, X1.20
SPI4_MISO: IC4.4, X1.12
SPI4_MOSI: IC4.5, X1.14
SPI5_CLK: IC4.25, X1.23
SPI5_CSA: IC4.157, X1.29
SPI5_CSB: IC4.156, X1.31
SPI5_IRQ: IC4.79, JP8.2, X1.33
SPI5_MISO: IC4.26, X1.25
SPI5_MOSI: IC4.27, X1.27
VDD: C13.1, C14.1, C15.1, C16.1, C17.1, C18.1, C19.+, C20.1, C21.1, C22.1, C23.1, C24.1, C25.1, C26.1, C27.1, C28.1, C29.1, C30.1, FB1.P$1, IC4.15, IC4.23, IC4.36, IC4.49, IC4.62, IC4.72, IC4.82, IC4.96, IC4.99, IC4.118, IC4.131, IC4.136, IC4.149, IC4.159, IC4.171, IC4.172, JP1.NO, JP2.NO, R11.1, R17.2
~FAULT: IC3.1, IC4.58, R13.2, X1.26, X2.15
~RESET: IC3.4, IC4.31, IC7.4, IC17.29, JP4.NC, R11.2, X1.24, X4.15
